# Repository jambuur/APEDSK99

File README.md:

# APEDSK99 (Arduino Peripheral Expansion for the TI-99/4a)

### *July 2025 Newsflash: WiFi suggestion*
I did get a number of questions regarding a WiFi option using the Arduino WiFi shield. Initial investigation suggested a lack of memory so to make it fit I had to reduce other functionality. This I didn't want to do. However, there is a simple solution. There are devices that accept a wired Ethernet connection and bridges this to a WiFi network of your choice. It works a treat. Check out IOGEAR etc.

### *July 2024 Newsflash: IDEDSR adaption*
I am currently trying to adapt Fred Kaal's version of the DSR for Thierry Nouspikel's IDE card to APEDSK99. Not sure of a successful outcome yet as there are major design and hardware differences to take into account; the first experiments are encouraging though. If it works it will be a valuable addition to APEDSK99 as you would be able to mount and use existing MAME HD images on your TI. It will also save me from the big headache of trying to define APEDSK99 as a new device in MDOS (see below).

### *January 2024 Newsflash: Case 3D design files available*
With the help of an Industrial Design student I have finalised a case for APEDSK99, (loosely) following the style of the Speech Synthesizer. 
On a side note, I have been able to lay my hands on a Myarc Geneve card. As I don't have a PE Box I am building a standalone system including a modified APEDSK99 for booting and floppy / HD emulation. 

### *February 2023 Newsflash: Major Update in progress*

Check the TI Italian User Club for a review of the new version: https://www.ti99iuc.it/web/index.php?pagina=articoli&artid=219#.Y-gqDi9BxaS

Currently working on updating this Github page, Youtube channel etc. Biggest takeaway is that APEDSK99 is now pretty much plug and play. 
I am thinking of either supplying pre-assembled APEDSK99 shields, leaving it to you to source a cheap Arduino UNO + Ethernet Shield combo from Ebay, AliExpress etc.
Alternatively, I could supply complete kits; I have also been approached by a web shop interested in the same. 
Stay tuned :-) 

### *Arduino-based DSKx emulator / 32K / FTP / NTP shield for the TI99/4a*

APEDSK99 is an Arduino shield that emulates 3 DS/SD/80T floppy drives for the TI99/4a home computer. Combined with a Arduino UNO and an Ethernet / SD shield it allows you to load, save and use disk floppy images (DOAD) on a SD card or FTP server. It includes the necessary 32K RAM expansion and adds NTP date and time to BASIC. The APEDSK99 shield plugs directly into the side port and is powered separately from a USB cable. 

Like the TI, APEDSK99 is based on good old through-hole technology. The TI<->shield interface is the familiar design, with 74HCT541 buffers for address lines and a bi-directional 74LS245 buffer for the databus.  A 64Kx8 RAM stores the DSR code and provides the 32K RAM expansion. CRU is emulated through memory mapped addresses, simplifying shield design. A user-selectable binary DSR file is loaded into RAM at >4000 by the Arduino at powerup / reset. 

The Arduino UNO controls the TI interface, has R/W access to RAM, can halt the TI and tries to act as a FD1771. As GPIO pins are in rather short supply, Arduino RAM addressing is serial-to-parallel through 74HC595 shift registers. 

A status LED indicates APEDSK99 access as well as showing possible error codes.

The DSR is still very much the original TI Disk Controller ROM, but adapted to interface with a reliable SD card instead of wonky floppies. 
DSR code optimisation made enough RAM available to include some useful BASIC CALL routines. I think it's rather nice that most of the orginal programmers' blood, sweat and tears lives on.

### *How does it work?*

When the TI issues disk controller commands by writing to the various FD1771 registers, the Arduino receives an interrupt on one of its GPO pins. This interrupt is generated by a GAL which monitors A0, A13, A14, A15, WE* and MEMEN* sideport signals. On receiving an interrupt, the Arduino then:

1. halts the TI by making READY low; this simultaneously enables the shift registers
2. disables the sideport interface buffers
3. enables the Arduino RAM control bus
4. executes the command including updating the relevant FD1771 and CRU "registers"
5. executes the opposite of steps 3, 2 and 1

The GAL also does the memory decoding for the 32K memory expansion.

### *DOAD's*

DOAD's are stored in root folders on the SD card or on a FTP server. Default APEDSK99 files include a DISKS folder with a bunch of useful images to get you started. DOAD filenames must follow the DOS 8.3 format and have a ".DSK" extension. At powerup or reset the Arduino looks for optional \_APEDSK1.DSK / \_APEDSK2.DSK / \_APEDSK3.DSK_ files and maps them accordingly so you can have your favourite apps ready to go. The DSR includes all necessary CALL's for DOAD and DSK management.

Once a DOAD is mapped to a particular DSK, it behaves very much like a normal (but rather speedy) floppy. 

Regarding FTP, on my setup (a Linux server with VSFTP within the same LAN segment) I get about ~22Kbyte upload / download speed. In practice it means 6-7 seconds between the TI-BASIC FTP CALL for a SS/SD image and back to the friendly flashing cursor.

### *BASIC support*

The DSR includes some 15 additional BASIC CALL's but there is really only one to remember, **CALL AHLP**:

**CALL ARST** resets APEDSK99 including reloading the current DSR. It is a handy way to get your DOAD mappings to their default state. It is functionally the same as pressing the Arduino reset button and sort of the same but not really as power cycling. 

**CALL LDIR** list the DOAD's in the current selected directory on the SD card, displaying the DOAD name, TI DISK name and DSK characteristics:

**CALL SMAP** shows the current DSKx -> DOAD mappings, extended info and the available directories on the SD Card:

**CALL TIME** gets the current date and time from an NTP server. If you define a BASIC variable NTP$ of exactly 16 characters before the CALL, the NTP data will be stored for use in your programs:

NTP is also used in the background to update a DSK's timestamp when creating/changing files or formatting.
<br/>
<br/>

**CALL ACHR** redefines the "lower capital" character definitions to true lower case. It's a bit of a bummer that BASIC constantly reloads the original definitions in command mode so you can really only enjoy lower case characters while running a BASIC program. What has this feature  to do with DSK's I hear you ask? Well, nothing really but it gives you an example of developing useful CALL's with APEDSK99: 

**CALL LDSK** list the files on a DSK; I always thought that was a really nice feature of the C64 so here it is. LDSK uses the last DSK\# that was accessed if you ommit the [1-3] parameter:

**CALL PDSK** and **CALL UDSK** apply or remove a virtual "sticker tab" (remember those?). With the "tab" applied, APEDSK99 can't write to the DSK. Under the hood the Protected flag at 0x10 in the Volume Information Block is set/reset:

**CALL MDSK** maps DSK[1-3] to a DOAD. The DOAD file name is the DOS max 8 character part without the extension (see **CALL LDIR** above).  

**CALL NDSK** renames a mapped DOAD. The TI DISK name is set to match the DOAD 8 character name. With renaming the DSK, the current mapping is deleted as the DOAD has now a new name. This command is handy for quickly creating a freshly formatted DSK. Just **FGET** a clean image (I use either FLOPPYSS.DSK or FLOPPYDS.DSK) and rename accordingly.

**CALL CDIR** changes the working directory. The SD Card image contains a /DISKS folder with lots of goodies and a /BLANK directory with the abovementioned clean images. One restriction is that you have to create additional directories on an external system as there is no CALL for that. 

**CALL RDSK** removes a DOAD from the SD card. In line with BOFH standards no confirmation is required but the DSK in question needs to be UNprotected.

**CALL FGET** and **CALL FPUT** load or save a DOAD from your FTP server of choice. Similar to **RDSK**, to overwrite an existing DSK on the SD card it needs to be UNprotected. To prevent overwriting images on your FTP server simply make them read-only.

**CALL ADSR** loads a DSR file from the SD card and resets APEDSK99. If the DSR file doens't exist or is invalid the default file APEDSK99.DSR will be loaded instead. The current DSR filename is stored in EEPROM so will survive resets and powerdowns. After loading a DSR, a soft-reset may be required to execute any DSR powerup routines. 

NB: 
**LDIR** and **LDSK** can generate multiple screens of info. A ">" will show up at the bottom right for you to press either \<SPACE\> for the next screen or \<ENTER\> to go back to the BASIC prompt.

### *APEDSK99 configuration*
Configuring APEDSK99 is easy. All it takes is to run a BASIC program called ACFG from DSK1:

The program has to run from TI BASIC (why? see _What about Extended BASIC_ below):

The programs shows the current configuration before asking for updates. 

The new configuration is then applied to APEDSK99. If NTP is successfully configured the program shows the local date and time. The configuration is saved in EEPROM and used with every reset / powerup:

### *What about Extended BASIC*
Yes, good question as I take it EXBAS is used over TI BASIC by the majority TI enthusiasts. Obviously I wanted to support vanilla console users (like the ones re-entering the hobby after xx years such as myself). But that doesn't explain why EXBAS couldn't be used to run the configuration program. Well, the problem is that EXBAS doesn't support external CALL's in programs, only from the command line. This would mean you have to type in a set of commands instead of a more or less automated setup. Not a good idea I thought.

**UPDATE 16/1/2024**: I now have provided EXBAS support through CALL LINK as an alternative to execute DSR CALL code, for example CALL LINK("MDSK",1,"ACFG"). Adapting the configuration program to EXBAS is left as an exercise to the reader.

### *Ignition sequence*

The DSR containes a powerup routine (the original TI DISK Controller routine if fact) that needs to be executed before you can properly use DSK's.
So switch on the TI first, apply power to APEDSK99, wait a second for APEDSK99 to load the DSR (short flash from the LED) and then soft-reset the TI with \<FCTN\>-\>QUIT\> to execute the DSR powerup routine.

### *Error codes*

The LED can flash in the following intricate error patterns:

1. *flash*            : SPI / SD Card fault/not ready
2. *flash-flash*      : can't read DSR binary image (/xxxxxxxx.DSR)
3. *flash-flash-flash*: no valid DSR header (>AA) at DSR RAM >4000

### *Uploading Sketches*

You should make sure APEDSK99 is idle or even better, switch off the TI before uploading the APEDSK99 sketch from the Arduino IDE. If you don't, there is a slight chance the Arduino bootloader gets corrupted and you'll need a second Arduino to restore it. Yes I have been there.  

Alternatively you could connect [_Analog 1_ to _+5V_](img/A15V.jpg) with a jumper wire before uploading; this disables the APEDSK99 sideport buffer IC's so you can leave the TI powered on. In fact, if you intend to put APEDSK99 in some sort of case, plan a switch for this. It's not only handy for uploading sketches but also for temporarily circumventing _TI Extended BASIC_'s LOAD feature.

### *Updating the DSR*

I compile the DSR .a99 file with [xtd99 TI99 cross development tools](https://endlos99.github.io/xdt99/) and then use [this hex editor](https://mh-nexus.de/en/hxd/) for padding the binary file with zero's to the full 8KB. After that it's just a matter of saving the binary file as APEDSK99.DSR in the root of the SD.

### Feeling Brave - DIY from scratch

If you decide to build one yourself, I have compiled a handy document to get you started. Just ping me with any questions through Github, YouTube or AtariAge (JJB).

### A suitable case

I have teamed up with an Industrial Design student from a local university and have come up with the design below. It (very) roughly follows the design of the Speech Synthesizer and has a handy hatch to access the SD card and reset button:

### *I know*

Writing software is a hobby, not my profession. No doubt some gurus would achieve the same functionality with half the code. But I dare to say that at least the basic DSR I/O routines in the sketch are reasonably efficient, useful and fast. Anyway I am content with dusting off that stack of virtual floppies, have a beer and admire my work. 

Feel free to improve and share!

### *Bugs*

If a particular program or module behaves nicely by accessing disks solely through the regular DSR routines there shouldn't be any new ones (are there any existing disk controller bugs?) In other words, any funky index hole math or weird copy protection schemes will likely fail. 

Not so much a bug but an annoyance is that the FAT format (as used on the SD Card) doesn't support any sorting whatsover; so if you have been actively **FGET**'ing images from your FTP server you might find the **SDIR** list slightly out of alphabetical order. There are a number of "FAT Sorter" programs for different OS's that can restore the order for you (the one I use is included in the repository).

And yes, if I had thought it through a bit more I would have designed APEDSK99 with the USB and Ethernet connectors facing backwards. Anyway what's done is done and unless there is a push for a major revision (unlikely) you'll (we) have to live with this minor inconvenience.

### *Future*

After (of course) I came up with the name APEDSK99 I realised that DSK emulation is just a first application. The APEDSK99 shield is actually a generic interrupt-driven DSR interface to a substantial catalogue of available Arduino shields. Also, the Arduino has full access to the 32K RAM expansion and since it uses a 64Kx8 RAM chip there is an additional 24K available for additional DSR, program code or device data sharing.

### *Acknowledgements*

This project owes a lot to Thierry Nouspikel's marvelous [TI Tech Pages website](http://www.unige.ch/medecine/nouspikel/ti99/disks.htm) which has a wealth of information on the TI Disk Controller, including a commented disassembly of its DSR ROM.

Another great source of information has been Monty Schmidt's excellent book [Technical Drive](img/MSTDrive.jpg). Monty went on to do great things, check out [SoundForge](https://www.magix.com/us/music/sound-forge/). Monty has now made his book publically availabe: https://github.com/wuntusk/technical-drive

The Arduino's serial-to-parallel RAM addressing scheme is neither new or mine but I have gratefully used part of [this excellent project](https://github.com/mkeller0815/MEEPROMMER) by Mario Keller.

Last but not least I virtually stumbled across my old friend Frederik "Fred" Kaal who I hadn't seen for 30 years after moving to the other side of the globe. Long live the Web and places such as AtariAge. Fred was a TI wizzard back then and [still very much is](http://ti99-geek.nl). His expert input has been of great help.

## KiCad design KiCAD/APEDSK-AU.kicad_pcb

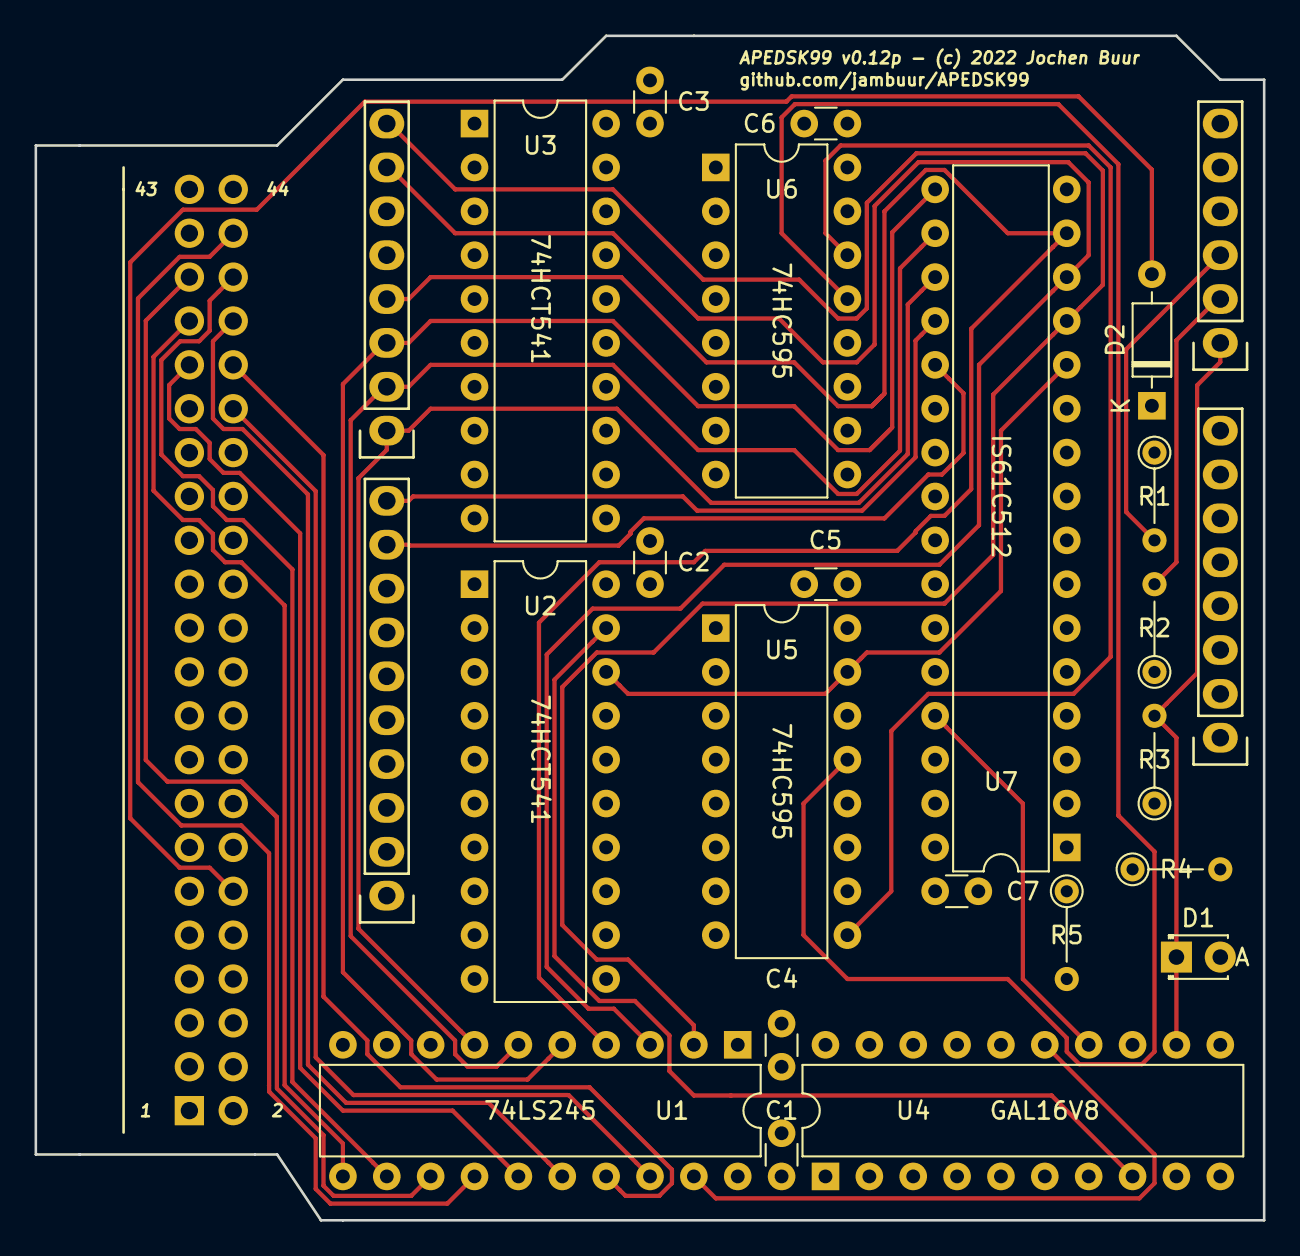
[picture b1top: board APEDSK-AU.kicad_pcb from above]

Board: 4 copper layers, 71.1 x 68.6 mm, 26 parts (1 on the bottom side), 45 nets.

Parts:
C1, C2, C3, C4, C5, C6, C7: 100N; C_Disc_D3.0mm_W1.6mm_P2.50mm
D1: ~CE; LED_D1.8mm_W3.3mm_H2.4mm
D2: 1N4148; D_DO-35_SOD27_P7.62mm_Horizontal
J1: 240-44-44Pins; PinHeader_2x22_P2.54mm_Vertical
P1: Power; Socket_Strip_Arduino_1x08
P2: Analog; Socket_Strip_Arduino_1x06
P3: Digital; Socket_Strip_Arduino_1x10
P4: Digital; Socket_Strip_Arduino_1x08
R1, R2, R3: 5.1K; R_Axial_DIN0204_L3.6mm_D1.6mm_P5.08mm_Vertical
R4: 330R; R_Axial_DIN0204_L3.6mm_D1.6mm_P5.08mm_Vertical
R5: 1K; R_Axial_DIN0204_L3.6mm_D1.6mm_P5.08mm_Vertical
U1: 74LS245; DIP-20_W7.62mm
U2, U3: 74LS541; DIP-20_W7.62mm
U4: GAL16V8; DIP-20_W7.62mm
U5, U6: 74HC595; DIP-16_W7.62mm
U7: IS61C512-20M; DIP-32_W7.62mm

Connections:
+5V: C1.2, C2.1, C3.1, C4.1, C5.1, C6.1, C7.1, P1.5, R1.1, R2.1, R3.1, R4.1, U1.20 (VCC), U2.20 (VCC), U3.20 (VCC), U4.20 (VCC), U5.10 (~SRCLR), U5.16 (VCC), U6.10 (~SRCLR), U6.16 (VCC), U7.30 (CE2), U7.32 (VCC)
/A0: J1.31, U3.9 (A7)
/A1: J1.30, U3.8 (A6)
/A2: J1.20, U3.7 (A5)
/A3: J1.10, U3.6 (A4)
/A4: J1.7, U3.5 (A3)
/A5: J1.5, U3.4 (A2)
/A6: J1.29, U3.3 (A1)
/A7: J1.17, U3.2 (A0)
/A8: J1.14, U2.9 (A7)
/A9: J1.18, U2.8 (A6)
/A10: J1.6, U2.7 (A5)
/A11: J1.8, U2.6 (A4)
/A12: J1.11, U2.5 (A3)
/A13: J1.15, U2.4 (A2)
/A14: J1.16, U2.3 (A1)
/A15: J1.19, U2.2 (A0)
/AD_A0: U2.11 (Y7), U2.12 (Y6), U2.13 (Y5), U2.14 (Y4), U2.15 (Y3), U2.16 (Y2), U2.17 (Y1), U2.18 (Y0), U4.5 (I5), U5.1 (QB), U5.2 (QC), U5.3 (QD), U5.4 (QE), U5.5 (QF), U5.6 (QG), U5.7 (QH), U5.15 (QA), U7.5 (A7), U7.6 (A6), U7.7 (A5), U7.8 (A4), U7.9 (A3), U7.10 (A2), U7.11 (A1), U7.12 (A0)
/AD_A10: U3.11 (Y7), U3.12 (Y6), U3.13 (Y5), U3.14 (Y4), U3.15 (Y3), U3.16 (Y2), U3.17 (Y1), U3.18 (Y0), U4.2 (I2), U4.3 (I3), U4.4 (I4), U6.1 (QB), U6.2 (QC), U6.3 (QD), U6.4 (QE), U6.5 (QF), U6.6 (QG), U6.7 (QH), U6.15 (QA), U7.3 (A14), U7.4 (A12), U7.23 (A10), U7.25 (A11), U7.26 (A9), U7.27 (A8), U7.28 (A13), U7.31 (A15)
/AD_D0: P3.9, P3.10, P4.1, P4.2, P4.3, P4.4, P4.7, P4.8, U1.2 (A0), U1.3 (A1), U1.4 (A2), U1.5 (A3), U1.6 (A4), U1.7 (A5), U1.8 (A6), U1.9 (A7), U7.13 (D0), U7.14 (D1), U7.15 (D2), U7.17 (D3), U7.18 (D4), U7.19 (D5), U7.20 (D6), U7.21 (D7)
/CE_245: U1.19 (CE), U4.15 (IO5)
/CLOCK: P2.4, U5.11 (SRCLK), U6.11 (SRCLK)
/D0: J1.37, U1.11 (B7)
/D1: J1.40, U1.12 (B6)
/D2: J1.39, U1.13 (B5)
/D3: J1.42, U1.14 (B4)
/D4: J1.35, U1.15 (B3)
/D5: J1.38, U1.16 (B2)
/D6: J1.36, U1.17 (B1)
/D7: J1.34, U1.18 (B0)
/DBIN: J1.9, U1.1 (A->B)
/DS: P2.6, U5.14 (SER)
/LATCH: P2.5, U5.12 (RCLK), U6.12 (RCLK)
/READY: D2.2 (A), J1.12
/~AD_CE: D1.1 (K), P2.1, R3.2, U4.12 (IO8), U7.22 (~CE1)
/~AD_WE: P2.3, R1.2, U4.14 (IO6), U7.29 (~WE)
/~AR_BUF: D2.1 (K), P4.5, U5.13 (~OE), U6.13 (~OE)
/~MEMEN: J1.32, U4.7 (I7)
/~TIBUF: P2.2, R2.2, U2.1 (G1), U2.19 (G2), U3.1 (G1), U3.19 (G2), U4.8 (I8)
/~TI_INT: P4.6, R5.1
/~WE: J1.26, U4.6 (I6)
GND: C1.1, C2.2, C3.2, C4.2, C5.2, C6.2, C7.2, J1.21, J1.23, J1.25, J1.27, P1.6, P1.7, U1.10 (GND), U2.10 (GND), U3.10 (GND), U4.1 (I1/CLK), U4.9 (I9), U4.10 (GND), U4.11 (I10/~OE), U5.8 (GND), U6.8 (GND), U7.16 (GND), U7.24 (~OE)
unnamed: D1.2 (A), R4.2
unnamed: R5.2, U4.13 (IO7)
unnamed: U5.9 (QH'), U6.14 (SER)

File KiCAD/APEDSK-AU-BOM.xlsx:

Refercence | Type | Volume | Notes
C1-C7 | 100N ceramic | 7
D1 | 3mm LED | 1
D2 | 1N5711 | 1 | Schottky; 1N4148 etc works as well
J1 |  | 1 | Industrial Card Edge Slot Socket Connector 22x2P 44P 2.54mm 0.1" 3A * 240-44
P1 |  | 1 | Arduino stackable header pack
P2 |  | 1 | Arduino stackable header pack
P3 |  | 1 | Arduino stackable header pack
P4 |  | 1 | Arduino stackable header pack
R1-R3 | 5.1K | 3
R4 | 330R | 1
U1 | 74LS245 | 1 | 74HCT245 should work as well (not tested)
U2, U3 | 74LS541 | 2 | 74HCT541 works as well
U4 | GAL16V8 | 1
U5, U6 | 74HC595 | 2 | 74HCT595 should work as well (not tested)
U7 | IS61C512-20M | 1

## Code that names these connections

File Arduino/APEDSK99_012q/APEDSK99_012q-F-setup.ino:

void setup() {
  
  pinAsOutput(TI_BUFFERS);                                              //enable* or disable 74HCT541 address buffers and GAL outputs
  pinAsOutput(TI_READY);                                                //halt TI by making READY low; this enables the 74HC595 shift registers (and vice versa)

  TIstop();                                                             //halt TI, enable 74HC595 shift registers and give Arduino RAM control

  pinAsOutput(ETHSD_SS);                                                //initialise shield SS pin
  digitalHigh(ETHSD_SS);                                                //without this SPI subsystem won't work
  
  if ( !SD.begin(SPI_CS) ) {                                            //SD card present and can be initialized?              
    Flasher( 1 );                                                       //nope -> flash LED error 1
  }

  //74HC595 shift register control
  pinAsOutput(CLOCK);
  pinAsOutput(LATCH);
  pinAsOutput(DS);
 
  //read DSR binary from SD and write into DSR RAM
  if ( EEPROM.read(EEPROMDSR) == 0xFF ) {                               //invalid DSR (i.e. virgin Uno EEPROM or invalid DSR filename)?
    EEPROM.put( EEPROMDSR, "APEDSK99.DSR\0" );                          //yes, put default in EEPROM ...
  }
  char DSRtoload[13] = "\0";                                            //fresh char array
  EEPROM.get( EEPROMDSR, DSRtoload );                                   //get DSR filename from EEPROM
  if ( SD.exists(DSRtoload) ) {                                         //does it exist? ...
    File fileDSR = SD.open( DSRtoload, FILE_READ );                     //yes; write DSR data to APEDSK99 RAM
    for ( unsigned int ii = 0x4000; ii < 0x6000; ii++ ) {
      write_DSRAM( ii, fileDSR.read() );                                                
    }
    
    fileDSR.close();
  } else {
    EEPROM.write( EEPROMDSR, 0xFF);                                     //... no; mark DSR invalid so default gets restored at next boot
    Flasher( 2 );                                                       //flash error 2
  }
  
  if ( read_DSRAM(0x4000) != 0xAA ) {                                   //valid DSR mark (>AA) at first DSR RAM byte?  
    EEPROM.write( EEPROMDSR, 0xFF);                                     //no; mark DSR invalid
    Flasher( 3 );                                                       //loading DSR unsuccessful -> flash error 3
  }

  //initialise DSKx Active and Protect flags
  for ( byte ii = 0; ii < 3; ii++ ) {
    if ( SD.exists( nameDSK[ii] ) ) {                                   //does DOAD x exist?
      activeDSK[ii] = true;                                             //yes; flag active
      DSKx = SD.open( nameDSK[ii], FILE_READ );                         //open DOAD file to check write protect y/n
      DSKx.seek( 0x10 );                                                //byte 0x10 in Volume Information Block stores Protected status
      protectDSK[ii] = DSKx.read();                                     //0x50 || "P" means disk is write protected 
      DSKx.close();                                                     //close current SD DOAD file
    }
  } 
  
  //"initialize FD1771"
  FD1771reset();                                                        //"Restore" command
  noExec();                                                             //"no command" as default
    
  //GAL flag: A0-A2, A15(=0,MSB), MEMEN* and WE* -> IO7(pin 13)
  //signals a write to DSR space (aka CRU, FD1771 registers) ... 
  //... or read sector/track with R6 counter in RAM; see DSR source)
  pinAsInputPullUp(TI_INT);                                             //from Ethernet SS to detecting TI Interrupts 

  TIgo();                                                               //TI: take it away
  
} //end of setup()

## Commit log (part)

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2020-03-30 UPDATE
    update
2020-04-07 cleanup
2020-04-11 adsr
2020-04-15 Spelling
2020-04-15 buffer length
2020-04-21 multiple MDSK() calls
    Multiple MDSK() calls mapping only the last DOAD against the previous drive
2020-04-29 Added SDIR() command
2020-05-28 A15 to 74LS138/E3
    In preparation for Ethernet connectivity 74LS138 E3 (part of interrupt generation) is now directly connected to TI A15 instead of AD_D0. No interrupt pulse present anymore on TI_INT during Arduino pr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
2020-08-21 Added R5 for D2:TI_INT/ETH_CS shared use
2020-08-26 1K protection resistor TI_INT/ETH_CC; R6 ipv R4 for jump table index
2020-08-28 fix display issue with SDIR() and LDSK()
2020-08-28 LDSK() switch DSK during ">" fix
2020-09-06 added R6 noise supression resistor
2021-02-04 README.MD
2021-02-04 update pics
2021-02-04 APEETH99 -> APEDSK99
2021-03-11 Update APEDSK99_012o-C-dsr_msg_ntp.ino
    adjust AHLP for 8C ADSR
2021-04-26 Silkscreen update
2021-11-23 Streamline PLD
2022-01-03 Update APEDSK99_012o-B-CONFIG.ino
    fixed faulty NTP server example format
2022-01-03 TIME
    removed automatic date / time printing from TIME command
2022-01-03 Update APEDSK99.a99
    removed automatic date / time printing from TIME command
2022-06-21 KiCad V6 / D2
    Migrated project to KiCad v6
    Replaced R6 with D2 to remove video interference
2022-06-21 ISO C++
    moved to strict ISO C++ code
2022-06-21 version 12.p
    Sync version with KiCad project
2022-06-24 updated images
2022-06-25 Update APEDSK99_012p-B-CONFIG.ino
    -warning on non-standard comma's in IPAddress
    -added comment to change TZ to local timezone
2022-06-29 Gerber + drill file
    Gerber + drill file for JCLPCB
2022-07-25 time zone; side info
    -added available time zones
    - streamlined sides display in SDIR
2022-07-25 DEFINE
2022-07-26 version control
2022-07-26 support libs
2022-07-26 support libraries
2022-07-29 optimisation
2022-07-30 Revert "optimisation"
    This reverts commit 97ca5f435ea7aff5f6439de7219d267c08f4082a.
2022-07-30 Revert "library version"
    This reverts commit c7d360221b5625b5f0667dc25140103a4f7425d1.
2022-07-30 IP section
2022-10-06 polling change
2022-11-09 INT to POLL
    improved timing and sync with TI
2022-11-16 different GROM 0 versions
2022-11-16 QA wincupl
2022-11-30 12p->12q reduced memory footprint
2022-11-30 12p->12q rename
2022-12-01 MDSK/RDSK/FGET/FPUT error
    These commands would generate an error if they were the first executed after a reset. (effectively DSK0--)
2022-12-03 Reduced memory footprint
2022-12-08 new version R
2022-12-10 towards DD/80T
2022-12-11 updated DSR for DD/80T
2022-12-12 SDSK update (more info)
2022-12-13 missing SDFat files
2022-12-15 from 2x16chars to 1x32chars display
2022-12-18 NDSK
    New rename DSK command. Better error checking on CALL's in DSR
2022-12-18 AHLP, array bugs
2022-12-20 error check, added NDIR
2022-12-24 folder functionality
2022-12-26 string argument process error fixed
2022-12-29 ALOW implementation
2022-12-30 improved AHLP, SDSK d/t bug
2022-12-30 proper AHLP array size
2022-12-31 minor edits
2022-12-31 NTP error handling bug
2023-01-03 error/help display optimise
2023-01-06 artifacts in display output
2023-01-11 Ergonomics
2023-01-13 NDIR / MDSK bug
2023-01-13 Updated DSR (streamlined, LDSK trick)
2023-01-23 ARST, subcommand structure
2023-01-23 ARST version print; subcommand structure
2023-02-05 config / DSR unified version
    - APEDSK99 can now be configured through BASIC, no need to change/compile/upload sketch.
    - 1 unified DSR supporting the 3 different GROM 0 versions (HONK, SCROLL etc)
2023-02-06 preserving >A018 value
2023-02-10 XBAS extensions prep
2023-02-11 change branch
2023-02-11 Version info pointer
2023-02-12 pic updates
2023-02-12 img update
2023-02-18 EXBAS support
2023-02-19 EXBAS CALL LINK hooks
2023-02-21 help and error external
2023-03-09 string functions, module support
    - replaced memory-hungry strnxxx functions and sprintf() with homegrown versions
    - CALL LINK support added for E/A and MM
2023-03-09 CALL LINK
2023-03-09 CALL LINK, v12s
2023-03-10 new version 12s
    slimmed down to stay within memory limits when compiled with newer IDE's. CALL LINK now working for EA and MM
2023-03-12 8 character DSK bug / FAT sorter
2023-03-14 further reduction memory footprint
    quite a journey
2023-03-25 further footprint reduction
2023-04-13 documentation errors
2024-01-09 Update README.md
    Side note
2024-01-15 still playing around
2024-01-15 Myarc version not for public consumption (yet)
2024-01-17 schematic cleanup
2024-01-20 build instructions, case files
2024-01-23 KiCad FS error + updated BOM
2024-02-28 updated docs
2024-03-22 updated case 3D files

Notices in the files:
KiCAD/APEDSK-AU.kicad_pcb:
APEDSK99 v0.12p - (c) 2022 Jochen Buur
